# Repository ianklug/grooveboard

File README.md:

# Grooveboard
A four-key mechanical keyboard for rhythm games.

Design by [ianklug](https://ianklug.com). Art by [clue](https://clue.graphics).

Special thanks to [Sebastiaan Swinkels](https://github.com/C44Supra) for technical assistance.

Made with [KiCad](https://www.kicad.org/).

*Please clone this repository using the `--recurse-submodules` flag. Some of the required symbol and footprint libraries will not be included otherwise.*

## Versions

*Please note that the RP2040 models are functional at a hardware level, but software is incomplete.*

The 2.x versions (grooveboard-rp) use the RP2040 MCU, and require different firmware from the 1.x versions. They also include a few new features and refinements over the 1.x models, including M2 mounting holes and improved key spacing.

The 1.x versions (grooveboard-atmel) use the Atmega32U4 MCU, in either the MU or AU footprint. These versions are no longer recommended.

There are three types of Grooveboard, each supporting different types of switches.

**Grooveboard:** Compatible with MX, Choc, or Alps-style switches. Switches must be soldered.

**Grooveboard MX:** Compatible with MX-style switches only. Uses Kailh MX hot-swap sockets.

**Grooveboard Choc:** Compatible with Choc-style switches only. Uses Kailh Choc hot-swap sockets.

## Firmware

Grooveboard is powered by [QMK Firmware](https://qmk.fm).

Grooveboard ships by default with firmware supporting [VIA Configurator](https://caniusevia.com). To modify your keymap, install VIA Configurator, plug in your Grooveboard, and begin customizing. Changes will be applied immediately.

For more advanced functionality, you may also customize Grooveboard using [QMK Configurator](https://config.qmk.fm), or by using QMK on the command line. This will require a reflash of your board's firmware. Use [QMK Toolbox](https://github.com/qmk/qmk_toolbox) to flash if on Windows or MacOS, or the QMK CLI with avrdude on Linux.

## Manufacturing

**Manufacture at your own risk. I can not guarantee the quality or functionality of boards not sold directly by me.**

**Please note that most PCB manufacturers have a minimum order quantity of five units.**

Hand-soldering Grooveboards from scratch is extremely difficult and NOT recommended due to the small size of the surface-mount components and their pads. Instead, PCB assembly services can source and assemble all the small parts on the bottom of the board. Depending on the manufacturer, you may only need to hand-solder some of the larger parts, such as the USB port and the switches/sockets.

I can personally recommend [JLCPCB](https://jlcpcb.com) or [PCBWay](https://pcbway.com/), but most PCB manufacturers should be capable of producing Grooveboard.

Zipped gerber files are present for the production designs of each variation of Grooveboard. They are called `<variation>-gerbers-<version>.zip` and should be compatible with most PCB manufacturing services.

If you will be ordering from JLCPCB, use `<variation>-gerbers-jlcpcb-<version>.zip`. These gerbers have the JLCPCB serial number placed in an easily-readable location on the back of the board. Make sure to choose "Specify a location" under "Remove Order Number" so that this number is printed where expected.

Production Grooveboards are two-layer FR4, 1.6mm thick. The RP2040 versions measure 120x25mm. They are assembled using lead-free solder. BOM and Centroid files are present for each board in the format expected by JLCPCB.

The USB connector is a [GCT USB4085](https://gct.co/connector/usb4085). The hot-swap sockets are [Kailh sockets](https://www.kailhswitch.com/mechanical-keyboard-switches/box-switches/mechanical-keyboard-switches-kailh-pcb-socket.html). **Sockets are different for MX switches and Choc switches! Make sure to use the right kind for the model you have chosen.**

## License

Shield: [![CC BY-SA 4.0][cc-by-sa-shield]][cc-by-sa]

This work is licensed under a
[Creative Commons Attribution-ShareAlike 4.0 International License][cc-by-sa].

[![CC BY-SA 4.0][cc-by-sa-image]][cc-by-sa]

[cc-by-sa]: http://creativecommons.org/licenses/by-sa/4.0/
[cc-by-sa-image]: https://licensebuttons.net/l/by-sa/4.0/88x31.png
[cc-by-sa-shield]: https://img.shields.io/badge/License-CC%20BY--SA%204.0-lightgrey.svg

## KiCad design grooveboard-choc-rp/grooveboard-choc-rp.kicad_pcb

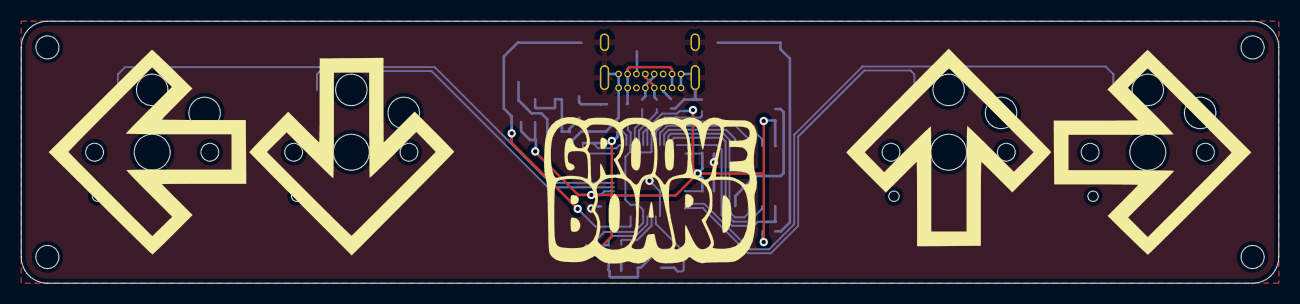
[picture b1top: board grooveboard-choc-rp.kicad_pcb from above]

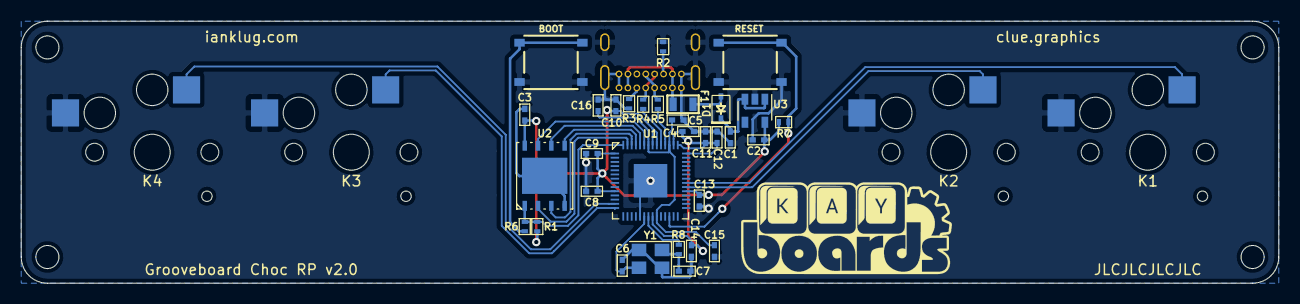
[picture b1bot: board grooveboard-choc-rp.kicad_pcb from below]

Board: 2 copper layers, 120.0 x 25.0 mm, 41 parts (32 on the bottom side), 27 nets.

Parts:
C1, C2: 10uF; C_0402
C3, C8, C9, C10, C11, C12, C13, C14, C15, C16: 100nF; C_0402
C4, C5: 1uF; C_0402
C6, C7: 10pF; C_0402
D1: 20V 1A; D_SOD-323
F1: 500mA; Fuse_0805
H1, H2, H3, H4: MountingHole; MountingHole_2.2mm_M2
J1: USB_C_Receptacle_USB2.0; USB_C_GCT_USB4085
K1, K2, K3, K4: MX-NoLED; Kailh_socket_PG1350
R1: DNP; R_0402
R2, R3: 5.1k; R_0402
R4, R5: 27; R_0402
R6, R8: 1k; R_0402
R7: 10k; R_0402
SW1: BOOT; TS-1187A-B-A-B
SW2: RESET; TS-1187A-B-A-B
U1: RP2040
U2: W25Q128JV; W25Q128JVPIQ
U3: AP2112K-3.3; SOT-23-5
Y1: 12MHz; Crystal_SMD_3225-4pin_3.2x2.5mm

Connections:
+5V: C1.1, D1.1, U3.1, U3.3
D+: J1.A6, J1.B6, R4.1
D-: J1.A7, J1.B7, R5.1
GND: C1.2, C2.2, C3.2, C4.2, C5.2, C6.2, C7.2, C8.2, C9.2, C10.2, C11.2, C12.2, C13.2, C14.2, C15.2, C16.2, J1.A1, J1.A12, J1.B1, J1.B12, J1.S1, K1.2, K2.2, K3.2, K4.2, R2.1, R3.1, SW1.1, SW2.2, U1.19, U1.57, U2.4, U3.2, Y1.2, Y1.4
K1: K1.1, U1.35
K2: K2.1, U1.34
K3: K3.1, U1.14
K4: K4.1, U1.13
unnamed: C7.1, R8.2, Y1.1
unnamed: D1.2, F1.1
unnamed: F1.2, J1.A4, J1.A9, J1.B4, J1.B9
unnamed: J1.A5, R3.2
unnamed: J1.B5, R2.2
unnamed: R4.2, U1.47
unnamed: R5.2, U1.46
unnamed: R6.1, SW1.2
unnamed: R7.1, SW2.1, U1.26
QSPI_0: U1.53, U2.5
QSPI_1: U1.55, U2.2
QSPI_2: U1.54, U2.3
QSPI_3: U1.51, U2.7
QSPI_SCLK: U1.52, U2.6
QSPI_SS: R1.2, R6.2, U1.56, U2.1
VREG_VIN: C2.1, C3.1, C4.1, C8.1, C9.1, C10.1, C11.1, C12.1, C13.1, C14.1, R1.1, R7.2, U1.1, U1.10, U1.22, U1.33, U1.42, U1.43, U1.44, U1.48, U1.49, U2.8, U3.5
VREG_VOUT: C5.1, C15.1, C16.1, U1.23, U1.45, U1.50
XIN: C6.1, U1.20, Y1.3
XOUT: R8.1, U1.21

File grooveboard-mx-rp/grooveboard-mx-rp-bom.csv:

Comment,Designator,Footprint,LCSC Part Number
10uF,"C1, C2",402,C15525
100nF,"C3, C8, C9, C10, C11, C12, C13, C14, C15, C16",402,C1525
1uF,"C4, C5",402,C52923
10pF,"C6, C7",402,C32949
Schottky,D1,SOD-323,C191023
500mA,F1,805,C261942 
10k,R7,402,C25744
5.1k,"R2, R3",402,C25905
27,"R4, R5",402,C1557
1k,"R6, R8",402,C25905
TS-1187A-B-A-B,"SW1, SW2",SMD,C318884 
RP2040,U1,QFN-56(7x7),C2040
W25Q128JV,U2,WSON-8_5x6mm,C190862
3.3V,U3,SOT-25,C51118
12MHz,Y1,SMD3225-4P,C255903

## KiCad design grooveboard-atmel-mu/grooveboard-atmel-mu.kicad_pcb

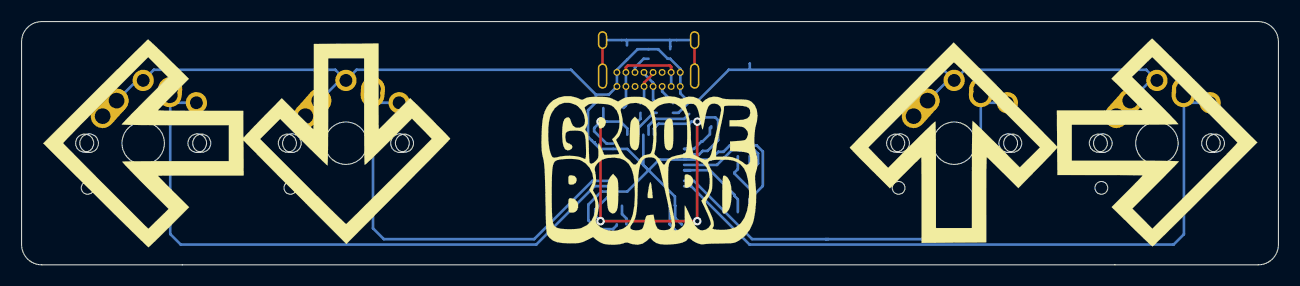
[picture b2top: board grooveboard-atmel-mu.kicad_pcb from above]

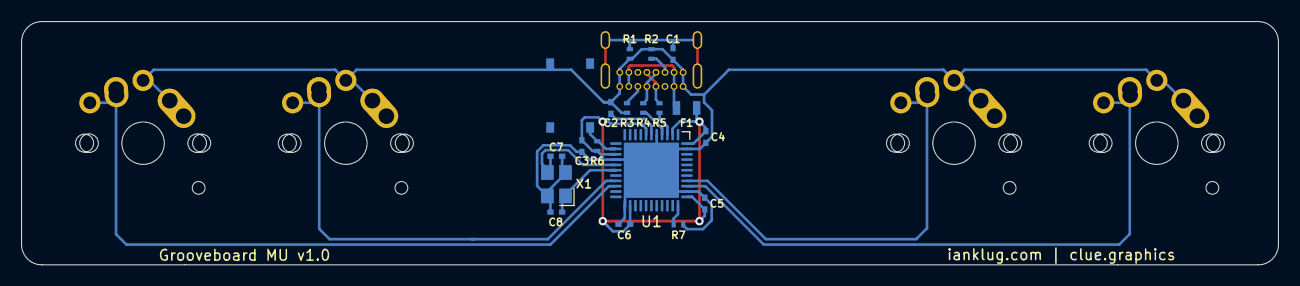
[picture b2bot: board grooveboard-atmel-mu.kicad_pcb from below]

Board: 2 copper layers, 118.1 x 22.9 mm, 24 parts (19 on the bottom side), 19 nets.

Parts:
C1: 4.7nF; C_0402
C2: 1uF; C_0402
C3, C4, C5: 0.1uF; C_0402
C6: 10uF; C_0402
C7, C8: 22pF; C_0402
F1: 500mA; Fuse_0805
J1: USB_C_Receptacle_USB2.0; USB_C_GCT_USB4085
MX1, MX2, MX3, MX4: MX-NoLED; MX-Alps-Choc-1U-NoLED
R1: 1M; R_0402
R2, R3: 5.1k; R_0402
R4, R5: 22; R_0402
R6, R7: 10k; R_0402
SW1: SW_Push; TS-1187A-B-A-B
U1: ATmega32U4-MU; QFN-44-1EP_7x7mm_P0.5mm_EP5.2x5.2mm
X1: 16MHz; Crystal_SMD_3225-4pin_3.2x2.5mm

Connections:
D+: R4.1, U1.4
D-: R5.1, U1.3
GND: C1.2, C2.2, C3.2, C4.2, C5.2, C6.2, C7.1, C8.1, J1.A1, J1.A12, J1.B1, J1.B12, MX1.2, MX2.2, MX3.2, MX4.2, R1.2, R2.1, R3.1, R7.1, SW1.1, U1.5, U1.15, U1.23, U1.35, U1.43, U1.45, X1.2, X1.4
MX1: MX1.1, U1.36
MX2: MX2.1, U1.37
MX3: MX3.1, U1.19
MX4: MX4.1, U1.20
unnamed: C1.1, J1.S1, R1.1
unnamed: C2.1, U1.6
unnamed: C7.2, U1.16, X1.3
unnamed: C8.2, U1.17, X1.1
unnamed: F1.2, J1.A4, J1.A9, J1.B4, J1.B9
unnamed: J1.A5, R3.2
unnamed: J1.A6, J1.B6, R4.2
unnamed: J1.A7, J1.B7, R5.2
unnamed: J1.B5, R2.2
unnamed: R7.2, U1.33
RST: R6.2, SW1.2, U1.13
VCC: C3.1, C4.1, C5.1, C6.1, F1.1, R6.1, U1.2, U1.7, U1.14, U1.24, U1.34, U1.44

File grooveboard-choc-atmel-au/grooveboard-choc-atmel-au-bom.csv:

Comment,Designator,Footprint,LCSC Part Number
4.7nF,C1,402,C1538
1uF,C2,402,C52923
100nF,"C3, C4, C5",402,C1525
10uF,C6,402,C15525
22pF,"C7, C8",402,C1555 
1M,R1,402,C26083
5.1k,"R2, R3",402,C25905
22,"R4, R5",402,C25092
10k,"R6, R7",402,C25744
500mA,F1,805,C261942 
ATmega32U4-AU,U1,TQFP-44_10.0x10.0x0.8P ,C44854
16MHz,X1,SMD-3225_4P ,C13738 
TS-1187A-B-A-B,SW1,SMD-SW-4_5.1x5.1x1.5 ,C318884

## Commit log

2021-05-09 Add basic readme
2021-05-09 add firmware
2021-05-09 include recurse-submodules in readme
2021-05-09 readme submodule info
2021-05-09 readme updates
2021-05-29 Update readme with warning
2021-05-29 qmk link
2021-05-29 readme ordering section
2021-06-29 add AU versions of hot swap boards
2021-06-29 Update README 2021-06-29
2021-06-30 add firmware for au and mu versions
2021-06-30 add firmwares for via configurator
2021-06-30 Readme update 2021-06-30
2021-06-30 Add flashing information
2021-06-30 unify firmware
2021-06-30 update board designs to unify key wiring and firmware
2021-06-30 Update README 2021-06-30
2021-07-01 update firmware
2021-07-13 update via definition
2021-07-13 update grooveboard photo
2021-07-14 Update firmware info
2021-07-24 update silkscreen issue
2021-11-11 Create LICENSE
2022-11-05 rp2040 initial commit
2022-11-17 fix incorrect resistor part number in BOM
2022-11-17 update usb resistors

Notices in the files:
parts and their libraries:
Copyright 2021 Accelerated Designs. All rights reserved.
